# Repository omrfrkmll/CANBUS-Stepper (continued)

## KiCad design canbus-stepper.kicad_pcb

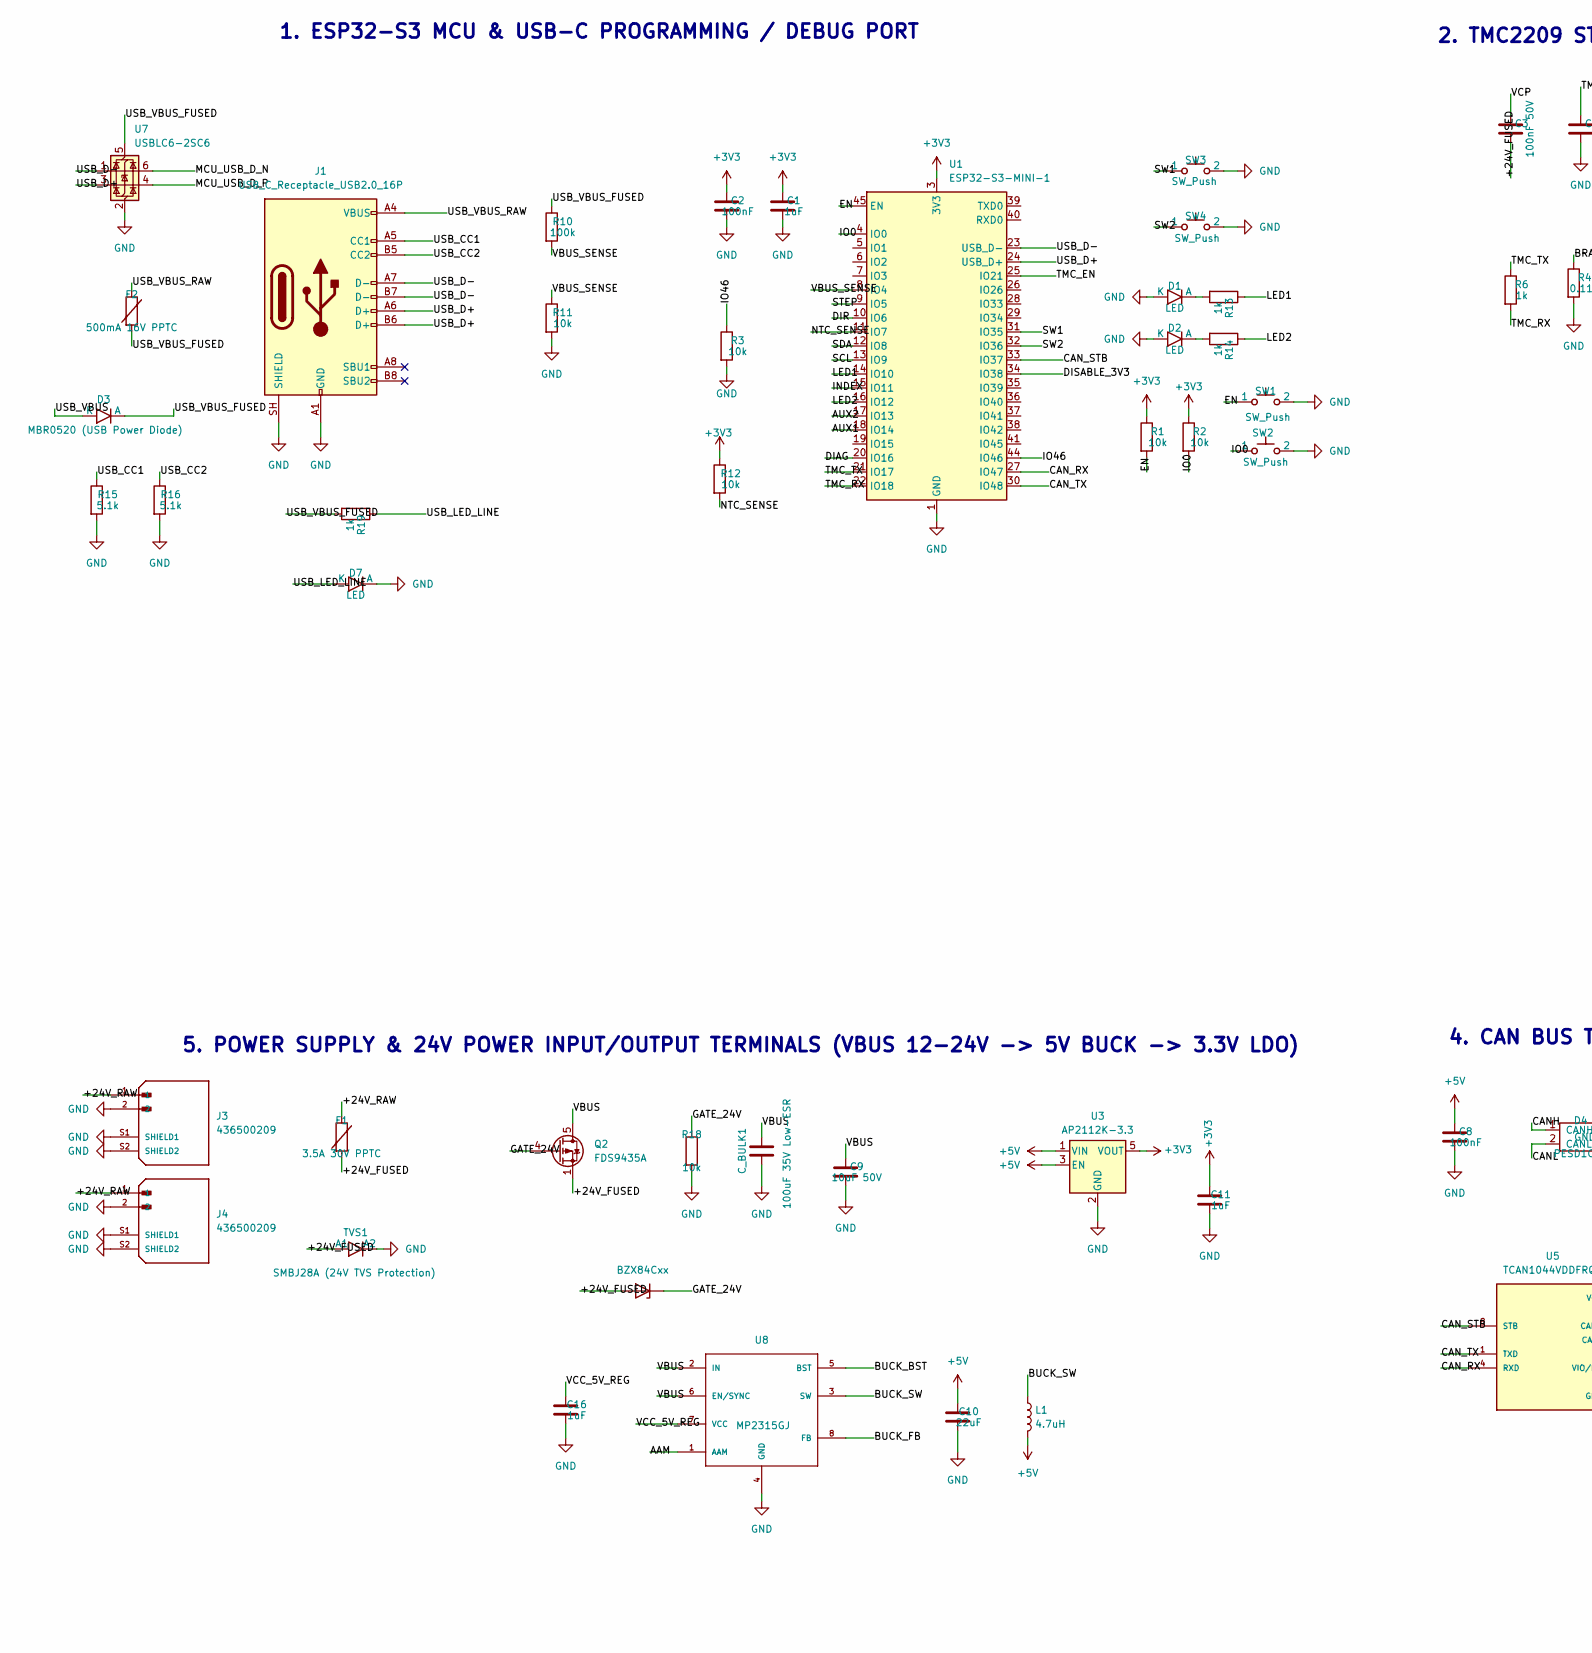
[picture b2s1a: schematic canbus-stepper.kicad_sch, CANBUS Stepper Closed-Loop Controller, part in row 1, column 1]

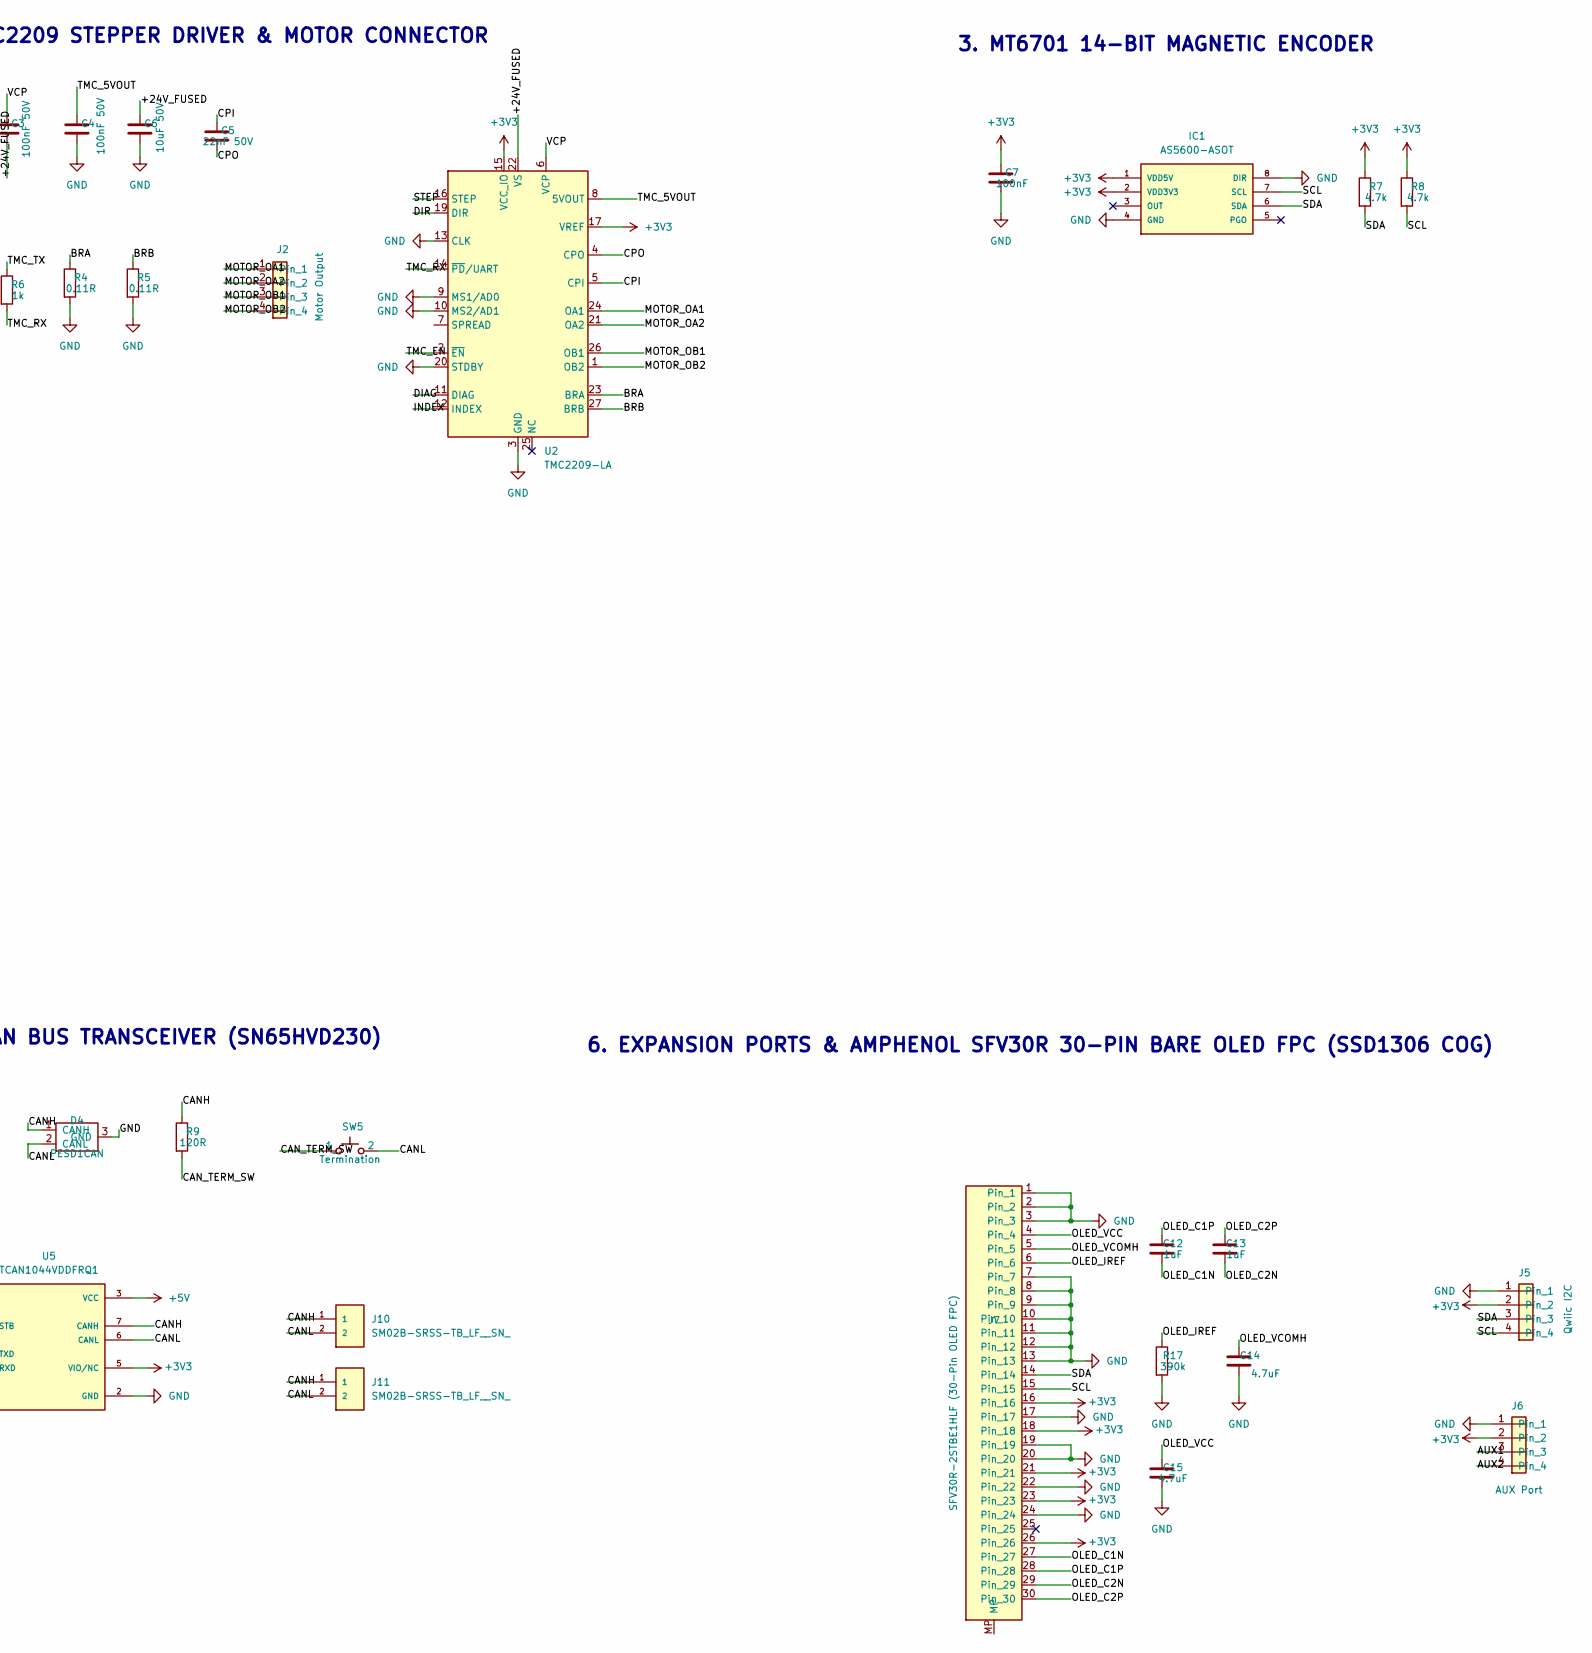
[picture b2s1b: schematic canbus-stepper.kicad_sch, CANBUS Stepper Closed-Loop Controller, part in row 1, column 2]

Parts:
C1, C11, C12, C13: 1uF; C_0603_1608Metric
C2, C7, C8: 100nF; C_0603_1608Metric
C3, C4: 100nF 50V; C_0603_1608Metric
C5: 22nF 50V; C_0603_1608Metric
C6, C9: 10uF 50V; C_1206_3216Metric
C10: 22uF; C_0805_2012Metric
C14, C15: 4.7uF; C_0603_1608Metric
C16: 1uF; C_0805_2012Metric
C_BULK1: 100uF 35V Low-ESR; CP_Elec_6.3x5.8
D1, D2, D7: LED; LED_0805_2012Metric
D3: MBR0520 (USB Power Diode); D_SOD-123
D4: PESD1CAN; SOT-23; LCSC PESD1CAN
D6: BZX84Cxx; SOT-23
F1: 3.5A 30V PPTC; Fuse_1812_4532Metric
F2: 500mA 16V PPTC; Fuse_0805_2012Metric
IC1: AS5600-ASOT; MOUSER_PART_NUMBER 985-AS5600-ASOT
J1: USB_C_Receptacle_USB2.0_16P; USB_C_Receptacle_16P; LCSC UJ20-C-H-G-SMT-4-P16-TR
J2: Motor Output; JST_S4B-PH-SM4-TB; LCSC S4B-PH-SM4-TB
J3: 436500209; MOLEX_436500209; PARTREV E2; LCSC 0436500209
J4: 436500209; MOLEX_436500209; PARTREV E2
J5: Qwiic I2C; JST_SH_SM04B-SRSS-TB_1x04-1MP_P1.00mm_Horizontal
J6: AUX Port; JST_SH_SM04B-SRSS-TB_1x04-1MP_P1.00mm_Horizontal
J7: SFV30R-2STBE1HLF (30-Pin OLED FPC); AMPHENOL_SFV30R-2STBE1HLF; LCSC SFV30R-2STBE1HLF
J10, J11: SM02B-SRSS-TB_LF__SN_; LCSC SM02B-SRSS-TB
L1: 4.7uH; L_0603_1608Metric
Q2: FDS9435A; SOIC-8_3.9x4.9mm_P1.27mm; LCSC AO4407A
R1, R2, R3, R11, R12, R18: 10k; R_0603_1608Metric
R4, R5: 0.11R; R_1206_3216Metric
R6, R13, R14, R19: 1k; R_0603_1608Metric
R7, R8: 4.7k; R_0603_1608Metric
R9: 120R; R_0603_1608Metric
R10: 100k; R_0603_1608Metric
R15, R16: 5.1k; R_0603_1608Metric
R17: 390k; R_0603_1608Metric
SW1, SW2: SW_Push; SW_TL3365AF180QG; LCSC TL3365AF180QG
SW3, SW4: SW_Push; SW_TS31-46-35-BK-B-160-RA-SMT-TR; LCSC TS31-46-35-BK-B-160-RA-SMT-TR
SW5: Termination; SW_DIP_SPSTx01_Slide_Copal_CHS-01A_W5.08mm_P1.27mm_JPin
TVS1: SMBJ28A (24V TVS Protection); D_SMB
U1: ESP32-S3-MINI-1; ESP32-S2-MINI-1; LCSC ESP32-S3-MINI-1-N4R2
U2: TMC2209-LA; VQFN-28-1EP_5x5mm_P0.5mm_EP3.7x3.7mm_ThermalVias; LCSC TMC2209-LA
U3: AP2112K-3.3; SOT-23-5; LCSC AP2112K-3.3TRG1
U5: TCAN1044VDDFRQ1; SOT65P280X110-8N; PARTREV C; LCSC TCAN1044VDDFR
U7: USBLC6-2SC6; SOT-23-6; LCSC USBLC6-2SC6_UMW
U8: MP2315GJ; SOT-23-8; MPN MP2315

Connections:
+3V3: C1.1, C2.1, C7.1, C11.1, IC1.1 (VDD5V), IC1.2 (VDD3V3), J5.2, J6.2, J7.16, J7.18, J7.21, J7.23, J7.26, R1.1, R2.1, R7.1, R8.1, R12.1, U1.3 (3V3), U2.15 (VCC_IO), U2.17 (VREF), U3.5 (VOUT), U5.5 (VIO/NC)
+5V: C8.1, C10.1, L1.2, U3.1 (VIN), U3.3 (EN), U5.3 (VCC)
/+24V_FUSED: C3.2, C6.1, D6.1 (A), F1.2, Q2.1 (S), Q2.2 (S), Q2.3 (S), TVS1.1 (A1), U2.22 (VS), U2.28 (VS)
/+24V_RAW: F1.1, J3.1, J4.1
/AAM: U8.1 (AAM)
/AUX1: J6.3, U1.18 (IO14)
/AUX2: J6.4, U1.17 (IO13)
/BRA: R4.1, U2.23 (BRA)
/BRB: R5.1, U2.27 (BRB)
/BUCK_BST: U8.5 (BST)
/BUCK_FB: U8.8 (FB)
/BUCK_SW: L1.1, U8.3 (SW)
/CANH: D4.1 (CANH), J10.1, J11.1, R9.1, U5.7 (CANH)
/CANL: D4.2 (CANL), J10.2, J11.2, SW5.2, U5.6 (CANL)
/CAN_RX: U1.27 (IO47), U5.4 (RXD)
/CAN_STB: U1.33 (IO37), U5.8 (STB)
/CAN_TERM_SW: R9.2, SW5.1
/CAN_TX: U1.30 (IO48), U5.1 (TXD)
/CPI: C5.1, U2.5 (CPI)
/CPO: C5.2, U2.4 (CPO)
/DIAG: U1.20 (IO16), U2.11 (DIAG)
/DIR: U1.10 (IO6), U2.19 (DIR)
/DISABLE_3V3: U1.34 (IO38)
/EN: R1.2, SW1.1, U1.45 (EN)
/GATE_24V: D6.3 (K), Q2.4 (G), R18.1
/INDEX: U1.15 (IO11), U2.12 (INDEX)
/IO0: R2.2, SW2.1, U1.4 (IO0)
/IO46: R3.1, U1.44 (IO46)
/LED1: R13.1, U1.14 (IO10)
/LED2: R14.1, U1.16 (IO12)
/MCU_USB_D_N: U7.6 (I/O1)
/MCU_USB_D_P: U7.4 (I/O2)
/MOTOR_OA1: J2.1, U2.24 (OA1)
/MOTOR_OA2: J2.2, U2.21 (OA2)
/MOTOR_OB1: J2.3, U2.26 (OB1)
/MOTOR_OB2: J2.4, U2.1 (OB2)
/NTC_SENSE: R12.2, U1.11 (IO7)
/OLED_C1N: C12.2, J7.27
/OLED_C1P: C12.1, J7.28
/OLED_C2N: C13.2, J7.29
/OLED_C2P: C13.1, J7.30
/OLED_IREF: J7.6, R17.1
/OLED_VCC: C15.1, J7.4
/OLED_VCOMH: C14.1, J7.5
/SCL: IC1.7 (SCL), J5.4, J7.15, R8.2, U1.13 (IO9)
/SDA: IC1.6 (SDA), J5.3, J7.14, R7.2, U1.12 (IO8)
/STEP: U1.9 (IO5), U2.16 (STEP)
/SW1: SW3.1, U1.31 (IO35)
/SW2: SW4.1, U1.32 (IO36)
/TMC_5VOUT: C4.1, U2.8 (5VOUT)
/TMC_EN: U1.25 (IO21), U2.2 (~EN)
/TMC_RX: R6.2, U1.22 (IO18), U2.14 (~PD/UART)
/TMC_TX: R6.1, U1.21 (IO17)
/USB_CC1: J1.A5 (CC1), R15.1
/USB_CC2: J1.B5 (CC2), R16.1
/USB_D+: J1.A6 (D+), J1.B6 (D+), U1.24 (USB_D+), U7.3 (I/O2)
/USB_D-: J1.A7 (D-), J1.B7 (D-), U1.23 (USB_D-), U7.1 (I/O1)
/USB_LED_LINE: D7.1 (K), R19.1
/USB_VBUS: D3.1 (K)
/USB_VBUS_FUSED: D3.2 (A), F2.2, R10.1, R19.2, U7.5 (VBUS)
/USB_VBUS_RAW: F2.1, J1.A4 (VBUS), J1.A9 (VBUS), J1.B4 (VBUS), J1.B9 (VBUS)
/VBUS: C9.1, C_BULK1.1, Q2.5 (D), Q2.6 (D), Q2.7 (D), Q2.8 (D), U8.2 (IN), U8.6 (EN/SYNC)
/VBUS_SENSE: R10.2, R11.1, U1.8 (IO4)
/VCC_5V_REG: C16.1, U8.7 (VCC)
/VCP: C3.1, U2.6 (VCP)
GND: C1.2, C2.2, C4.2, C6.2, C7.2, C8.2, C9.2, C10.2, C11.2, C14.2, C15.2, C16.2, C_BULK1.2, D1.1 (K), D2.1 (K), D4.3 (GND), D7.2 (A), IC1.4 (GND), IC1.8 (DIR), J1.A1 (GND), J1.A12 (GND), J1.B1 (GND), J1.B12 (GND), J1.SH (SHIELD), J3.2, J3.S1 (SHIELD1), J3.S2 (SHIELD2), J4.2, J4.S1 (SHIELD1), J4.S2 (SHIELD2), J5.1, J6.1, J7.1, J7.2, J7.3, J7.7, J7.8, J7.9, J7.10, J7.11, J7.12, J7.13, J7.17, J7.19, J7.20, J7.22, J7.24, R3.2, R4.2, R5.2, R11.2, R15.2, R16.2, R17.2, R18.2, SW1.2, SW2.2, SW3.2, SW4.2, TVS1.2 (A2), U1.1 (GND), U1.2 (GND), U1.42 (GND), U1.43 (GND), U1.46 (GND), U1.47 (GND), U1.48 (GND), U1.49 (GND), U1.50 (GND), U1.51 (GND), U1.52 (GND), U1.53 (GND), U1.54 (GND), U1.55 (GND), U1.56 (GND), U1.57 (GND), U1.58 (GND), U1.59 (GND), U1.60 (GND), U1.61 (GND), U1.62 (GND), U1.63 (GND), U1.64 (GND), U1.65 (GND), U2.3 (GND), U2.9 (MS1/AD0), U2.10 (MS2/AD1), U2.13 (CLK), U2.18 (GND), U2.20 (STDBY), U2.29 (GND), U3.2 (GND), U5.2 (GND), U7.2 (GND), U8.4 (GND); also elsewhere on the board
unnamed: D1.2 (A), R13.2
unnamed: D2.2 (A), R14.2

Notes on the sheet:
2. TMC2209 STEPPER DRIVER & MOTOR CONNECTOR
5. POWER SUPPLY & 24V POWER INPUT/OUTPUT TERMINALS (VBUS 12-24V -> 5V BUCK -> 3.3V LDO)
6. EXPANSION PORTS & AMPHENOL SFV30R 30-PIN BARE OLED FPC (SSD1306 COG)
1. ESP32-S3 MCU & USB-C PROGRAMMING / DEBUG PORT
4. CAN BUS TRANSCEIVER (SN65HVD230)
3. MT6701 14-BIT MAGNETIC ENCODER

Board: 2 copper layers, 69 parts (11 on the bottom side), 61 nets, no tracks yet.

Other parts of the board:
BOARD1: NEMA17_PCB_Outline; NEMA17_PCB_Outline_40.3x40.3_8Fillets

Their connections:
GND: BOARD1.H1, BOARD1.H1_V1, BOARD1.H1_V2, BOARD1.H1_V3, BOARD1.H1_V4, BOARD1.H1_V5, BOARD1.H1_V6, BOARD1.H1_V7, BOARD1.H1_V8, BOARD1.H2, BOARD1.H2_V1, BOARD1.H2_V2, BOARD1.H2_V3, BOARD1.H2_V4, BOARD1.H2_V5, BOARD1.H2_V6, BOARD1.H2_V7, BOARD1.H2_V8, BOARD1.H3, BOARD1.H3_V1, BOARD1.H3_V2, BOARD1.H3_V3, BOARD1.H3_V4, BOARD1.H3_V5, BOARD1.H3_V6, BOARD1.H3_V7, BOARD1.H3_V8, BOARD1.H4, BOARD1.H4_V1, BOARD1.H4_V2, BOARD1.H4_V3, BOARD1.H4_V4, BOARD1.H4_V5, BOARD1.H4_V6, BOARD1.H4_V7, BOARD1.H4_V8; also elsewhere on the board

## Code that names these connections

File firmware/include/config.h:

#pragma once

#include <Arduino.h>

// =============================================================================
// CANBUS-Stepper v1.1 Hardware Configuration & Pinout Map
// =============================================================================

// --- TMC2209-LA Stepper Driver Pins ---
#define PIN_TMC_STEP        33  // Step pulse input (IO33 / Pad 28)
#define PIN_TMC_DIR         34  // Direction control (IO34 / Pad 29)
#define PIN_TMC_EN          48  // Driver Enable (Active LOW) (IO48 / Pad 30)
#define PIN_TMC_TX          35  // ESP32 TX -> TMC2209 RX (UART) (IO35 / Pad 31)
#define PIN_TMC_RX          47  // ESP32 RX <- TMC2209 TX (UART) (IO47 / Pad 27)
#define PIN_TMC_DIAG        21  // StallGuard / Fault interrupt (IO21 / Pad 25)
#define PIN_TMC_INDEX       26  // Microstep index output (IO26 / Pad 26)

#define TMC_SERIAL_PORT     Serial1
#define TMC_BAUDRATE        115200
#define TMC_R_SENSE         0.11f  // 0.11 Ohm sense resistors (R4, R6 in schematic)
#define TMC_DRIVER_ADDRESS  0b00   // MS1=0, MS2=0 address

// --- AMS AS5600 12-Bit Magnetic Rotary Encoder ---
#define PIN_I2C_SDA         16  // Hardware I2C SDA (IO16 / Pad 20)
#define PIN_I2C_SCL         14  // Hardware I2C SCL (IO14 / Pad 18)
#define I2C_FREQUENCY       400000 // 400 kHz Fast-mode I2C
#define AS5600_I2C_ADDR     0x36

#define ENCODER_RESOLUTION  4096   // 12-bit (0 - 4095)
#define DEG_PER_COUNT       (360.0f / 4096.0f) // 0.08789 degrees per count

// --- CAN Bus / TWAI Transceiver (TI TCAN3413) ---
#define PIN_CAN_TX          38  // ESP32 TWAI TX (IO38 / Pad 34)
#define PIN_CAN_RX          37  // ESP32 TWAI RX (IO37 / Pad 33)
#define PIN_CAN_STB         39  // Standby pin (LOW = Normal Mode, HIGH = Standby) (IO39 / Pad 35)
#define DEFAULT_CAN_BAUD    500000 // 500 kbps default CAN baudrate (supports up to 1Mbps)
#define DEFAULT_CAN_NODE_ID 0x120  // Default Node ID for actuator

// --- Analog Sensing (ADC1) ---
#define PIN_VBUS_SENSE      2   // 24V/VBUS Voltage divider input (ADC1_CH1 / IO2 / Pad 6)
#define PIN_NTC_SENSE       3   // On-board / Motor NTC Thermistor (ADC1_CH2 / IO3 / Pad 7)

#define VBUS_R_TOP          100000.0f // 100k Ohm top divider (R20)
#define VBUS_R_BOTTOM       10000.0f  // 10k Ohm bottom divider (R14)
#define VBUS_DIVIDER_RATIO  ((VBUS_R_TOP + VBUS_R_BOTTOM) / VBUS_R_BOTTOM) // 11.0x

#define NTC_R_SERIES        10000.0f  // 10k series pull-up resistor (R3)
#define NTC_NOMINAL_R       100000.0f // 100k nominal resistance at 25C (NCU18WF104)
#define NTC_NOMINAL_TEMP    25.0f     // 25 °C
#define NTC_B_COEFFICIENT   4250.0f   // Beta coefficient (B25/50)

// --- User Controls & Status Indicators ---
#define PIN_LED1            1   // Status LED 1 (Heartbeat / Activity) (IO1 / Pad 5)
#define PIN_LED2            45  // Status LED 2 (CAN Activity / Warning) (IO45 / Pad 41)
#define PIN_SW1             6   // Tactile Switch 1 (User / Mode Select) (IO6 / Pad 10)
#define PIN_SW2             36  // Tactile Switch 2 (Calibrate / E-Stop) (IO36 / Pad 32)

// --- Expansion & Auxiliary GPIOs ---
#define PIN_AUX1            4   // AUX Header GPIO 1 / Endstop 1 (IO4 / Pad 8)
#define PIN_AUX2            5   // AUX Header GPIO 2 / Endstop 2 (IO5 / Pad 9)

// --- Motion & PID Default Parameters ---
#define DEFAULT_MICROSTEPS  16
#define STEPS_PER_REV_NEMA  (200 * DEFAULT_MICROSTEPS) // 3200 steps/rev for 1.8 deg motor
#define DEFAULT_MAX_VELOCITY 50000.0f // steps/s
#define DEFAULT_ACCEL       100000.0f // steps/s^2

#define PID_KP              2.5f
#define PID_KI              0.05f
#define PID_KD              0.12f
#define PID_LOOP_HZ         1000  // 1 kHz Closed-Loop Control Frequency
